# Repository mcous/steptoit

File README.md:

# Stepper Driver Board

## Parts to research / use
* Stepper driver - TI DRV8834
    * Up to 1/32 microstepping
    * 1.5 A continuous, 2.2 A peak
    * Step / direction control
    * Digikey qty 1: QFN: $2.98, TSOP: $3.53
* MCU - AVR ATMega328P
    * Cheap, simple, known
    * Probably underpowered in the long term
    * Tops out (apparently) at 16 MHz, and would like to go faster
* Steppers
    * check out http://www.mpja.com/
    * Start small

## To-do list
* Finalize(ish) parts list
* Design stepper control board
* Order stepper control board
* Order parts
* Design stepper testing frame
    * Three-axis linear movement table?
    * Three DOF rotational frame?
* Build stepper frame
* Assemble control board
* ???
* Profit!

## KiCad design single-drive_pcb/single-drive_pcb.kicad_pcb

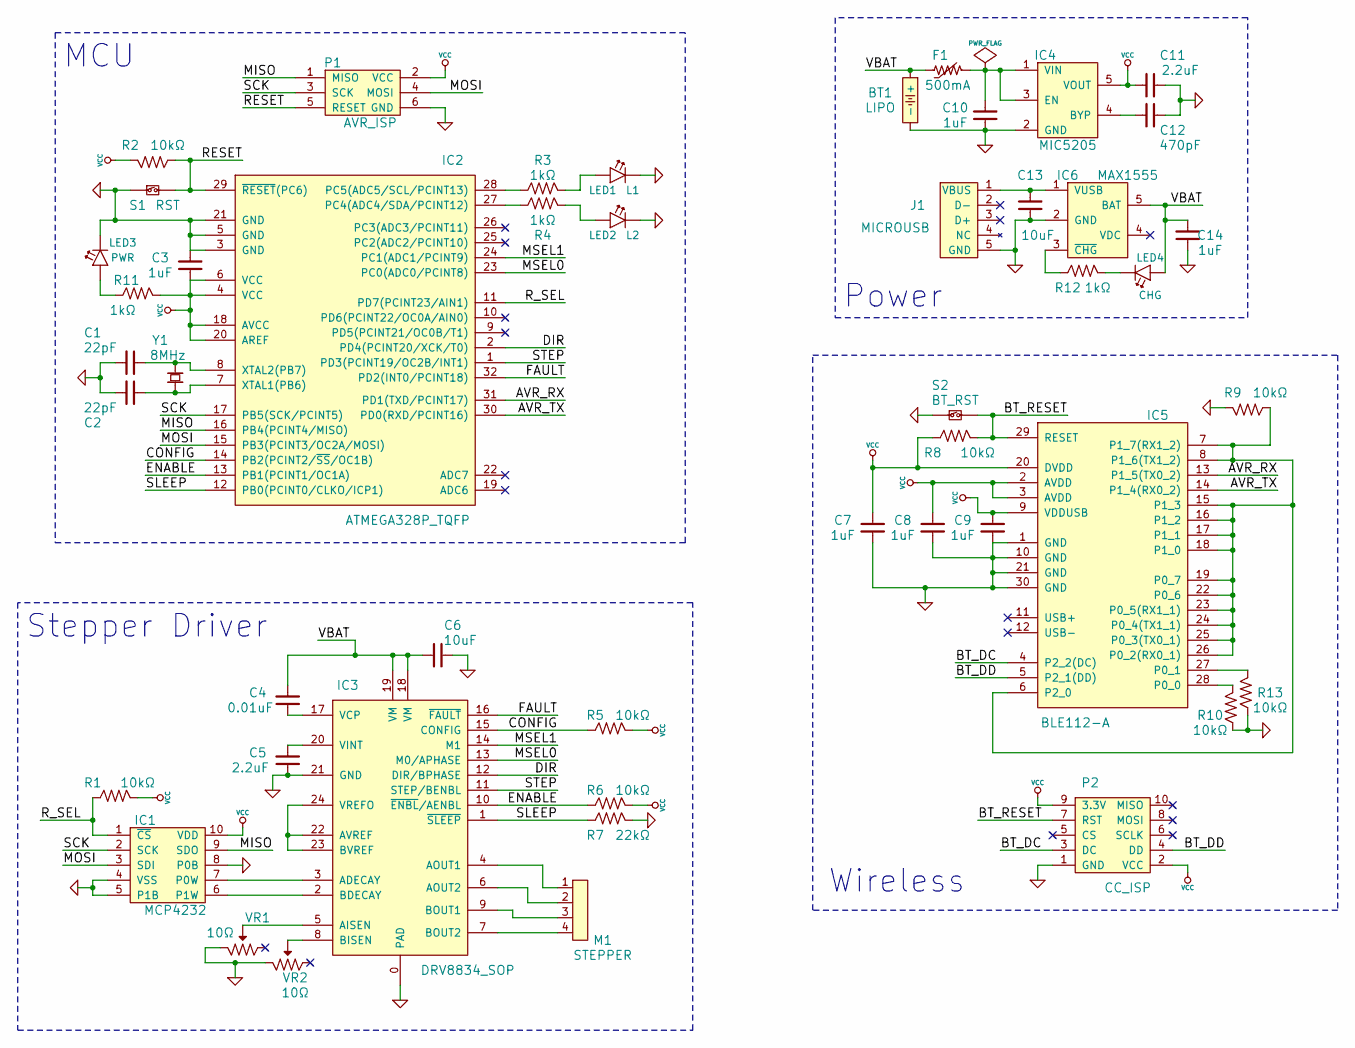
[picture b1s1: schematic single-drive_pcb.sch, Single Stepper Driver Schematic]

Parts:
BT1: LIPO
C1, C2: 22pF
C3, C7, C8, C9, C10, C14: 1uF
C4: 0.01uF
C5, C11: 2.2uF
C6, C13: 10uF
C12: 470pF
F1: 500mA
IC1: MCP4232
IC2: ATMEGA328P_TQFP
IC3: DRV8834_SOP
IC4: MIC5205
IC5: BLE112-A
IC6: MAX1555
J1: MICROUSB
LED1: L1
LED2: L2
LED3: PWR
LED4: CHG
M1: STEPPER
P1: AVR_ISP
P2: CC_ISP
R1, R2, R5, R6, R8, R9, R10, R13: 10kΩ
R3, R4, R11, R12: 1kΩ
R7: 22kΩ
S1: RST
S2: BT_RST
VR1, VR2: 10Ω
Y1: 8MHz

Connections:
/AVR_RX: IC2.31 (PD1(TXD/PCINT17)), IC5.13 (P1_5(TX0_2))
/AVR_TX: IC2.30 (PD0(RXD/PCINT16)), IC5.14 (P1_4(RX0_2))
/BT_DC: IC5.4 (P2_2(DC)), P2.3 (DC)
/BT_DD: IC5.5 (P2_1(DD)), P2.4 (DD)
/BT_RESET: IC5.29 (RESET), P2.7 (RST), R8.2, S2.2
/CONFIG: IC2.14 (PB2(PCINT2/~SS~/OC1B)), IC3.15 (CONFIG), R5.1
/DIR: IC2.2 (PD4(PCINT20/XCK/T0)), IC3.12 (DIR/BPHASE)
/ENABLE: IC2.13 (PB1(PCINT1/OC1A)), IC3.10 (~ENBL~/AENBL), R6.1
/FAULT: IC2.32 (PD2(INT0/PCINT18)), IC3.16 (~FAULT~)
/MISO: IC1.9 (SDO), IC2.16 (PB4(PCINT4/MISO)), P1.1 (MISO)
/MOSI: IC1.3 (SDI), IC2.15 (PB3(PCINT3/OC2A/MOSI)), P1.4 (MOSI)
/MSEL0: IC2.23 (PC0(ADC0/PCINT8)), IC3.13 (M0/APHASE)
/MSEL1: IC2.24 (PC1(ADC1/PCINT9)), IC3.14 (M1)
/RESET: IC2.29 (~RESET~(PC6)), P1.5 (RESET), R2.1, S1.2
/R_SEL: IC1.1 (~CS~), IC2.11 (PD7(PCINT23/AIN1)), R1.1
/SCK: IC1.2 (SCK), IC2.17 (PB5(SCK/PCINT5)), P1.3 (SCK)
/SLEEP: IC2.12 (PB0(PCINT0/CLKO/ICP1)), IC3.1 (~SLEEP~), R7.1
/STEP: IC2.1 (PD3(PCINT19/OC2B/INT1)), IC3.11 (STEP/BENBL)
/VBAT: BT1.1 (+), C4.1, C6.1, C14.2, F1.1, IC3.18 (VM), IC3.19 (VM), IC6.5 (BAT), LED4.2 (A)
GND: BT1.2 (-), C1.2, C2.1, C3.2, C5.1, C6.2, C7.1, C8.1, C9.1, C10.1, C11.2, C12.2, C13.1, C14.1, IC1.4 (VSS), IC1.5 (P1B), IC1.8 (P0B), IC2.3 (GND), IC2.5 (GND), IC2.21 (GND), IC3.0 (PAD), IC3.21 (GND), IC4.2 (GND), IC5.1 (GND), IC5.10 (GND), IC5.21 (GND), IC5.30 (GND), IC6.2 (GND), J1.5 (GND), LED1.1 (C), LED2.1 (C), LED3.1 (C), P1.6 (GND), P2.1 (GND), R7.2, R9.2, R10.1, R13.1, S1.1, S2.1, VR1.3 (E2), VR2.3 (E2)
unnamed: LED4.1 (C), R12.2
unnamed: C13.2, IC6.1 (VUSB), J1.1 (VBUS)
unnamed: IC3.22 (AVREF), IC3.23 (BVREF), IC3.24 (VREFO)
unnamed: LED3.2 (A), R11.1
unnamed: IC6.3 (~CHG~), R12.1
unnamed: C4.2, IC3.17 (VCP)
unnamed: IC1.7 (P0W), IC3.3 (ADECAY)
unnamed: IC3.9 (BOUT1), M1.3
unnamed: IC3.7 (BOUT2), M1.4
unnamed: IC3.4 (AOUT1), M1.1
unnamed: IC3.6 (AOUT2), M1.2
unnamed: C12.1, IC4.4 (BYP)
unnamed: C5.2, IC3.20 (VINT)
unnamed: IC5.27 (P0_1), R13.2
unnamed: IC5.28 (P0_0), R10.2
unnamed: IC5.6 (P2_0), IC5.7 (P1_7(RX1_2)), IC5.8 (P1_6(TX1_2)), IC5.15 (P1_3), IC5.16 (P1_2), IC5.17 (P1_1), IC5.18 (P1_0), IC5.19 (P0_7), IC5.22 (P0_6), IC5.23 (P0_5(RX1_1)), IC5.24 (P0_4(TX1_1)), IC5.25 (P0_3(TX0_1)), IC5.26 (P0_2(RX0_1)), R9.1
unnamed: IC1.6 (P1W), IC3.2 (BDECAY)
unnamed: IC3.5 (AISEN), VR1.2 (W)
unnamed: IC3.8 (BISEN), VR2.2 (W)
unnamed: LED2.2 (A), R4.2
unnamed: LED1.2 (A), R3.2
unnamed: C10.2, F1.2, IC4.1 (VIN), IC4.3 (EN)
unnamed: IC2.28 (PC5(ADC5/SCL/PCINT13)), R3.1
unnamed: IC2.27 (PC4(ADC4/SDA/PCINT12)), R4.1
unnamed: C1.1, IC2.8 (XTAL2(PB7)), Y1.2
unnamed: C2.2, IC2.7 (XTAL1(PB6)), Y1.1
VCC: C3.1, C7.2, C8.2, C9.2, C11.1, IC1.10 (VDD), IC2.4 (VCC), IC2.6 (VCC), IC2.18 (AVCC), IC2.20 (AREF), IC4.5 (VOUT), IC5.2 (AVDD), IC5.3 (AVDD), IC5.9 (VDDUSB), IC5.20 (DVDD), P1.2 (VCC), P2.2 (VCC), P2.9 (3.3V), R1.2, R2.2, R5.2, R6.2, R8.1, R11.2

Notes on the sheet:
Power
Wireless
MCU
Stepper Driver

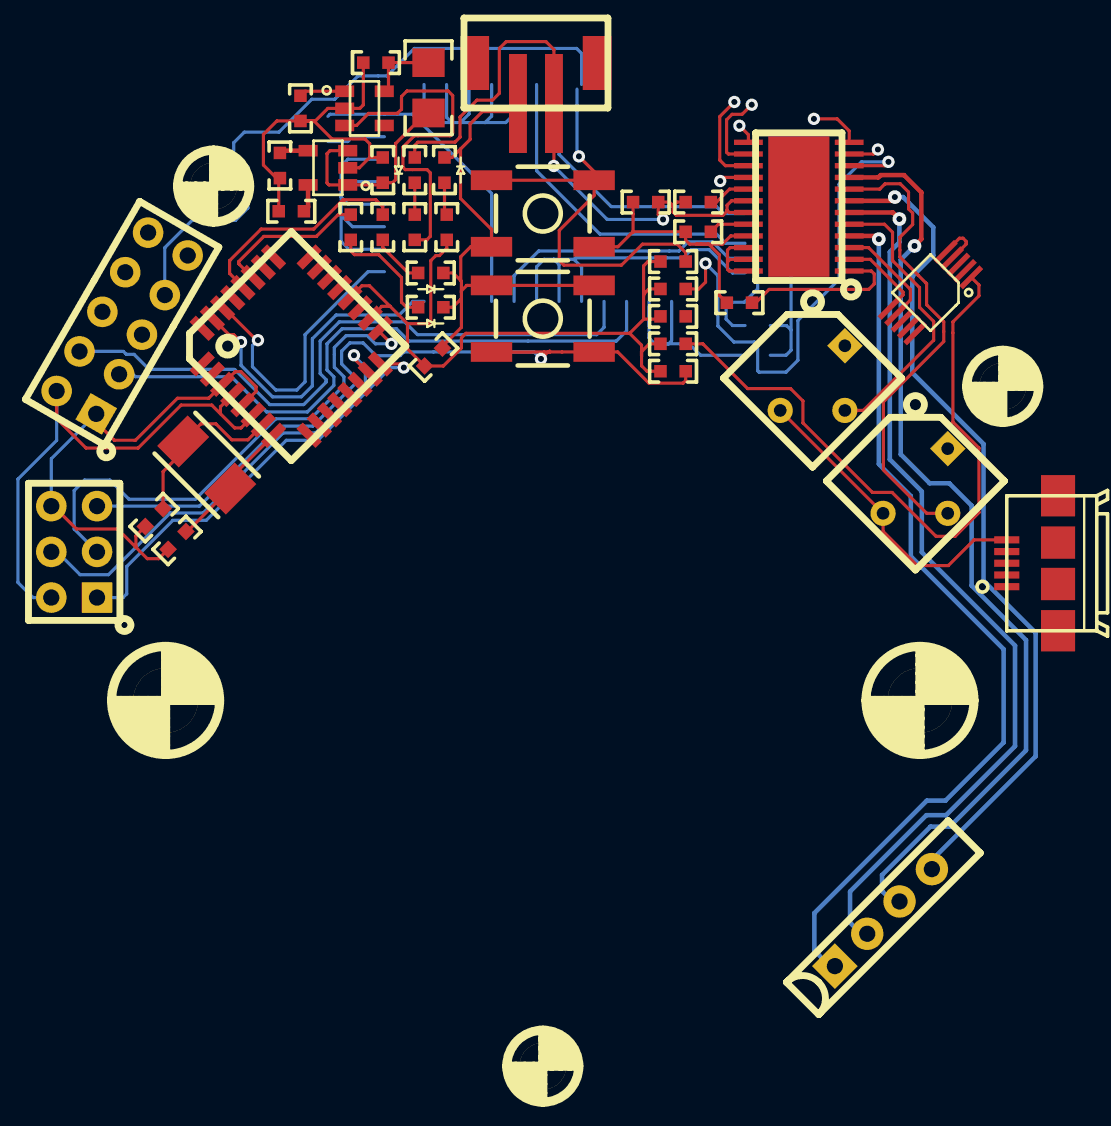
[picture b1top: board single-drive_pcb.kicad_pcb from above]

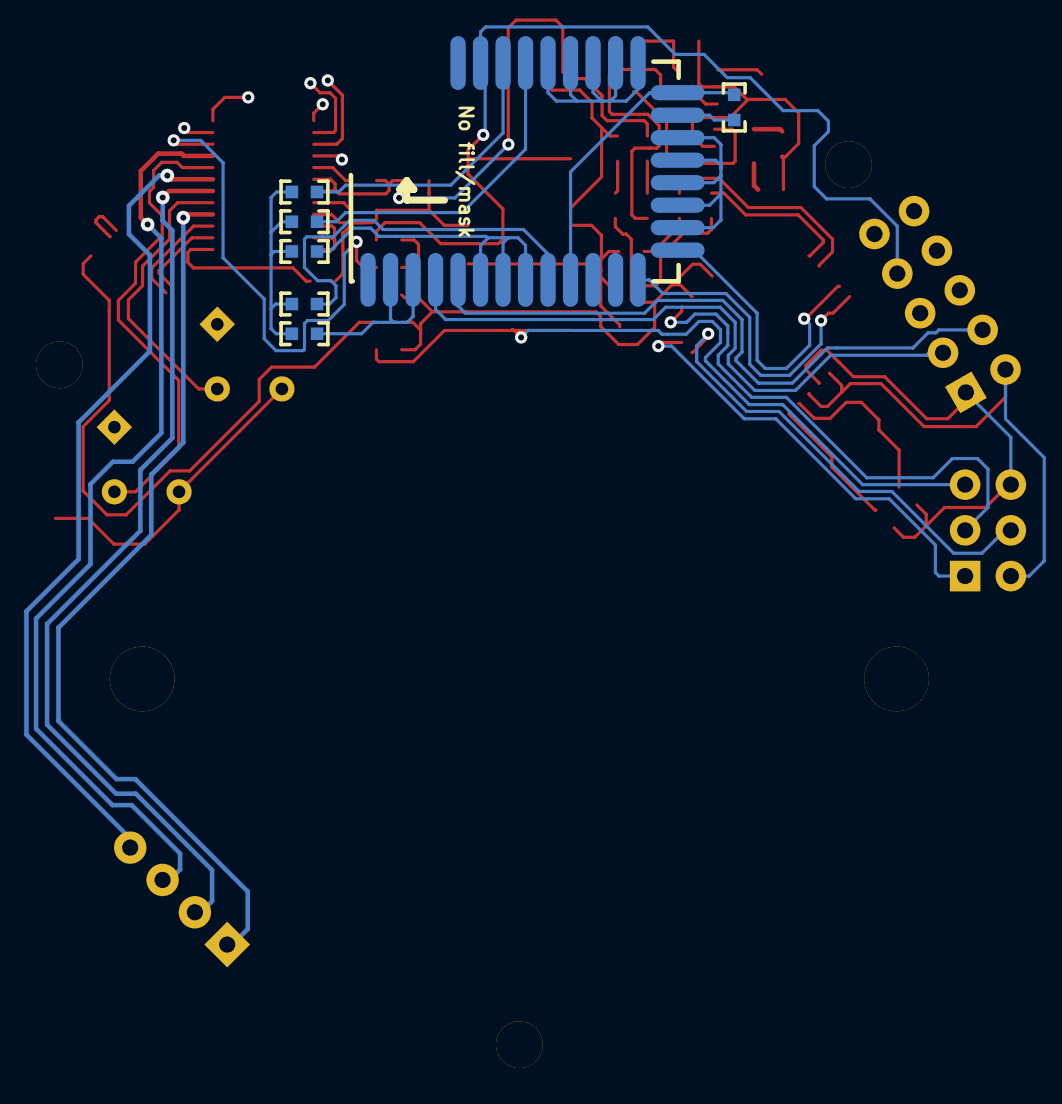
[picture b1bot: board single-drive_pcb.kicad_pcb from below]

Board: 2 copper layers, 53 parts (7 on the bottom side), 47 nets.

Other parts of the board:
M2, M2#2, M2#3: VAL**; M2
M3, M3#2: VAL**; M3

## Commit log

2013-07-04 dont panic
2013-07-12 pcb files for first stepper project
2013-07-12 added most of the components to the schematic and did some basic wiring
2013-07-17 added license
2013-07-18 refactored schematic for wirelessly controlled battery powered application
2013-07-19 added gitignore to ignore some temp kicad stuff my global doesn't catch
2013-07-19 added some pots to stepper current control
2013-07-19 schematic coming along
2013-07-19 schematic is done (until I find problems); moving on to footprint assignment
2013-07-19 added netlist to gitignore
2013-07-19 hey, remember that time I completely forgot to add a charging circuit to my battery powered project?
2013-07-19 added comonent to footprint file
2013-07-19 schematic done and footprints assigned
2013-07-19 added -bak files to gitignore
2013-07-19 started on pcb layout, need some dimensions before continuing
2013-07-20 trying out some stuff
2013-07-20 done for the day
2013-07-20 board might actually work. or, you know, it might not
2013-07-20 gonna take a break for a little while
2013-07-21 it's too late to be working on this

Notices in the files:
single-drive_pcb/single-drive_pcb.kicad_pcb:
Copyright 2013 by Michael Cousins
Released under the terms of the Creative Commons Attribution-ShareAlike 3.0 license
